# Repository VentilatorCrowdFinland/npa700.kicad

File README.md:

# NPA-7xx breakout board 

This board supports NPA-7xx series differential pressure sensors. 

## Board pinout 

1) VDD, 3.135 V to 3.465 V for NPA-730 series and 4.75 V to 5.25 V to NPA-700 series
2) PIN1 SCL
3) PIN2 SDA
4) PIN3 GPIO3 - Sensor version detect 1
5) PIN4 GPIO4 - Sensor version detect 2
6) PIN5 GPIO5 - Sensor version detect 3
7) PIN6 - NC, keying for assembly
8) GND

| GPIO3 | GPIO4 | GPIO5 | Sensor |
| ----- | ----- | ----- | ------ |
| HI    | HI    | LO/NC | Reserved     |
| LO/NC | HI    | LO/NC | NPA-7xx-030D |
| HI    | LO/NC | LO/NC | NPA-7xx-015D |
| LO/NC | LO/NC | LO/NC | NPA-7xx-005D |
| HI    | HI    | LO/NC | NPA-7xx-001D |
| LO/NC | HI    | LO/NC | NPA-7xx-10WD |
| HI    | LO/NC | LO/NC | NPA-7xx-05WD |
| LO/NC | LO/NC | LO/NC | NPA-7xx-02WD |

## Dimensions of expansion board

* Outline 17.5 x 32.5 mm (17.5 x 25 mm without mounting holes)
* Minimum drill 0.3 mm, annular 0.6 mm, trace 0.25 mm, isolation 0.15 mm.
* Any board thickness and plating.

## Exports
In addition to KiCAD source files, Gerbers and PDF export is available under exports of
each project folder.

## Versioning
Versions which begin with same letter (e.g. 'B') are interface-compatible: Their mounting holes
and signals are at the same places. Revisions might have internal changes, such as different routing or
component placement.

Versions which begin with different letter are not backward compatible, i.e. mounting holes or dimensions of board
may have changed. 

## Licenses

This board is based on [Ruuvi Connector board](https://github.com/ruuvi/connector) which is
CC BY-SA 4.0 licensed. 

Footprints are from 
 * [Ruuvi/KiCAD-library](https://www.ohwr.org/project/cernohl/wikis/uploads/8a6b5d01f71c207c49493e4d114d61e6/cern_ohl_p_v2_howto.pdf) 
which aren't licensed in any manner.
 * [ojousima.footprints.kicad](https://github.com/ojousima/ojousima.footprints.kicad/tree/0481a381fbb01a2b40545e94f72d81239064c85a) which is MIT-licensed.

A permission to publish this package under CERN-OHL-P has been requested, but not yet granted. In meanwhile, entire project inherits 
CC BY-SA from Ruuvi Connector design.

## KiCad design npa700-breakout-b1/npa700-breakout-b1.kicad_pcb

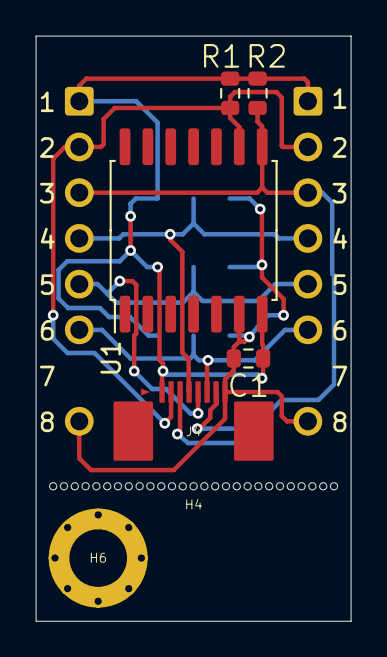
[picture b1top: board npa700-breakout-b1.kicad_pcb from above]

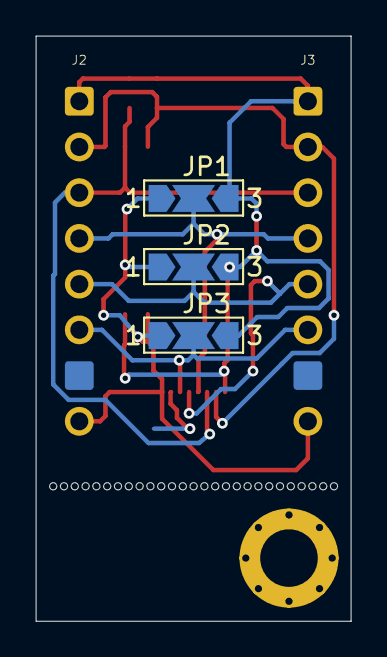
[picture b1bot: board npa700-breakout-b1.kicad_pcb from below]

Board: 2 copper layers, 17.5 x 32.5 mm, 12 parts (5 on the bottom side), 7 nets.

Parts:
C1: 100n; CAPC160X80X35L25N
H4: 27 x 0.4mm NPTH; BreakoutHoles
H6: MountingHole; MountingHole_3.2mm_M3_Pad_Via
J2, J3: Ruuvi Connector Pin Header; RUUVI_CONNECTOR_8PIN_HEADER
J4: Ruuvi Connector Horizontal; RUUVI_CONNECTOR_FFC
JP1, JP2, JP3: SolderJumper_3_Open; SolderJumper-3_P2.0mm_Open_TrianglePad1.0x1.5mm_NumberLabels
R1, R2: 10k; CAPC160X80X35L25N
U1: NPA-700; SOIC-14W_7.5x9mm_P1.27mm

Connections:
/GND: C1.1, J2.8, J3.8, J4.8, JP1.1, JP2.1, JP3.1, U1.6
/GPIO3: J2.4, J3.4, J4.4, JP1.2
/GPIO4: J2.5, J3.5, J4.5, JP2.2
/GPIO5: J2.6, J3.6, J4.6, JP3.2
/SCL: J2.2, J3.2, J4.2, R1.2, U1.9
/SDA: J2.3, J3.3, J4.3, R2.2, U1.8
/VDD: C1.2, J2.1, J3.1, J4.1, JP1.3, JP2.3, JP3.3, R1.1, R2.1, U1.7

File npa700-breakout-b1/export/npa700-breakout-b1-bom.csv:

"Id";"Designator";"Package";"Quantity";"Designation";"Supplier and ref";
1;"J3,J2";"RUUVI_CONNECTOR_8PIN_HEADER";2;"Ruuvi Connector Pin Header";;;
2;"H6";"MountingHole_3.2mm_M3_Pad_Via";1;"MountingHole";;;
3;"H4";"BreakoutHoles";1;"27 x 0.4mm NPTH";;;
4;"C1";"CAPC160X80X35L25N";1;"100n";;;
5;"R1,R2";"CAPC160X80X35L25N";2;"10k";;;
6;"U1";"SOIC-14W_7.5x9mm_P1.27mm";1;"NPA-700";;;
7;"J4";"RUUVI_CONNECTOR_FFC";1;"Ruuvi Connector Horizontal";;;
8;"JP1,JP2,JP3";"SolderJumper-3_P2.0mm_Open_TrianglePad1.0x1.5mm_NumberLabels";3;"SolderJumper_3_Open";;;

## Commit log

2020-04-10 Add libraries as submodules
2020-04-10 Add gitignore, remove DS_Store file
2020-04-10 First draft
2020-04-10 Add gerbers
2020-04-10 Rename board
2020-04-13 B1 files
2020-04-13 Fix table formatting
